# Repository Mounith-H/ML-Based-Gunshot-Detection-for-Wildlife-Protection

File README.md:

# AI-Powered Edge Gunshot Detection for Wildlife Protection

## Short summary
This repository contains firmware, hardware integration code, and supporting artifacts for an edge device that detects gunshot-like events using a Raspberry Pi Pico. The device performs on-device audio capture and inference, attaches GPS coordinates, and reports events over an NRF24L01 wireless link. The primary goals are real-time detection, low power operation, and field deployability for anti-poaching monitoring.

## Status
- Development: Feature-complete for core sensing, radio communication, GPS and power management on the Pico hardware.
- Machine learning: A TensorFlow Lite quantized model and export artifacts are provided; on-device inference integration is in progress.

Key completed items
- Audio input: INMP441 I2S microphone with PIO/DMA sampling.
- Location: NEO-6M GPS integration and basic NMEA parsing.
- Radio: NRF24L01 packet transmission with fragmentation and retries.
- Power: IP5306 power management using a PIO-driven PWM (continuous KEY pulsing) for reliable operation.
- Architecture: Dual-core Pico split (system/core tasks and audio/inference tasks) with robust initialization and error handling.

Planned / in development
- Finalize TensorFlow Lite inference on Pico and optimize model runtime.
- Optional mesh networking, encryption and acknowledgments.

## Repository contents (high level)
- `Raspberry_pi_pico/`, `inference-app/` – Pico firmware and build files.
- `python/` – training artifacts, quantized model (`gunshot_model_quant.tflite`), and helper notebooks.
- `python/dataset/` – dataset organization (environment and gunshot recordings) used for model training (see Data Availability).
- `figures_data/`, `metrics/` – plots, model metrics and training logs.
- `PCB/`, `lib/` – hardware design files and helper libraries.

## Data Availability (journal-ready statement)
All code required to build and run the device is included in this repository. The following datasets and artifacts are available as follows:

- Trained model: A quantized TensorFlow Lite model is included in `python/gunshot_model_quant.tflite` and additional exported models are in `python/exported_models/`.
- Processed training artifacts (training logs, metrics, and figure data) are included in `figures_data/` and `metrics/`.
- Raw audio recordings used for training (environmental and gunshot audio) are not included in this repository because of size and privacy/ethical constraints. Access to raw audio may be provided on reasonable request to the corresponding author for research purposes, subject to data sharing agreements.

If you need the raw audio files, preprocessed feature dumps, or a permanent DOI for the dataset, please contact the project maintainers (see Contact below). We can provide guidance to reproduce the training from raw data using the Jupyter notebook `python/model_training_quantization_jupyter.ipynb`.

Assumptions: The repository contains the trained model and training outputs, but large raw audio datasets are hosted externally or provided upon request. If you will publish this work in a journal and require a public dataset DOI, please tell us and we can prepare a dataset package for deposition (not currently included in this repo).

## Hardware
Components used in development
- Raspberry Pi Pico
- INMP441 digital microphone (I2S)
- NEO-6M GPS module
- NRF24L01 radio module
- IP5306 power-management IC

Power handling notes
- IP5306 `KEY` pin is driven by a PIO-based PWM to keep the power module enabled. The firmware contains a PIO state machine that pulses the `KEY` line with sufficient frequency and duty cycle to maintain power without manual intervention.
## Build and usage (Pico firmware)

Prerequisites

1. CMake >= 3.12
2. Raspberry Pi Pico SDK installed and `PICO_SDK_PATH` set in your environment

Quick build

1. From the firmware directory (for example `Raspberry_pi_pico/` or `inference-app/`):
   - mkdir build
   - cd build
   - cmake ..
   - make (or your platform's build tool)

2. Flashing

- Put the Pico into BOOTSEL mode and copy the generated `.uf2` file onto the Pico mass-storage device.

For exact build steps see the subdirectory `Raspberry_pi_pico/README.md` or `inference-app/README.md` (if present).

## Reproducing training
- A Jupyter notebook `python/model_training_quantization_jupyter.ipynb` demonstrates model training and quantization steps used to generate the included TFLite model. Use the `python/` directory for scripts and artifacts.

## Data sources and citations
The training used a combination of publicly available environmental and gunshot audio datasets. Below are the sources and citation information (BibTeX and IEEE formats).

1) E. Aydemir, "Gunshot audio dataset," Kaggle, 2021. [Online]. Available: https://www.kaggle.com/datasets/emrahaydemr/gunshot-audio-dataset. [Accessed: Oct. 11, 2025].

2) R. Kabealo and S. J. Wyatt, "Gunshot/Gunfire Audio Dataset," Zenodo, Jul. 2022, doi: 10.5281/zenodo.7004819. [Online]. Available: https://doi.org/10.5281/zenodo.7004819. [Accessed: Oct. 11, 2025].

3) K. J. Piczak, "ESC: Dataset for Environmental Sound Classification," in Proc. 23rd Annual ACM Conference on Multimedia, Brisbane, Australia, Oct. 2015, pp. 1015–1018, doi: 10.1145/2733373.2806390. [Online]. Available: http://dl.acm.org/citation.cfm?doid=2733373.2806390. [Accessed: Oct. 11, 2025].

## License and contact
- License: See `LICENSE` at the repository root for license terms.
- Contact / corresponding author: add a preferred contact email or GitHub handle here.

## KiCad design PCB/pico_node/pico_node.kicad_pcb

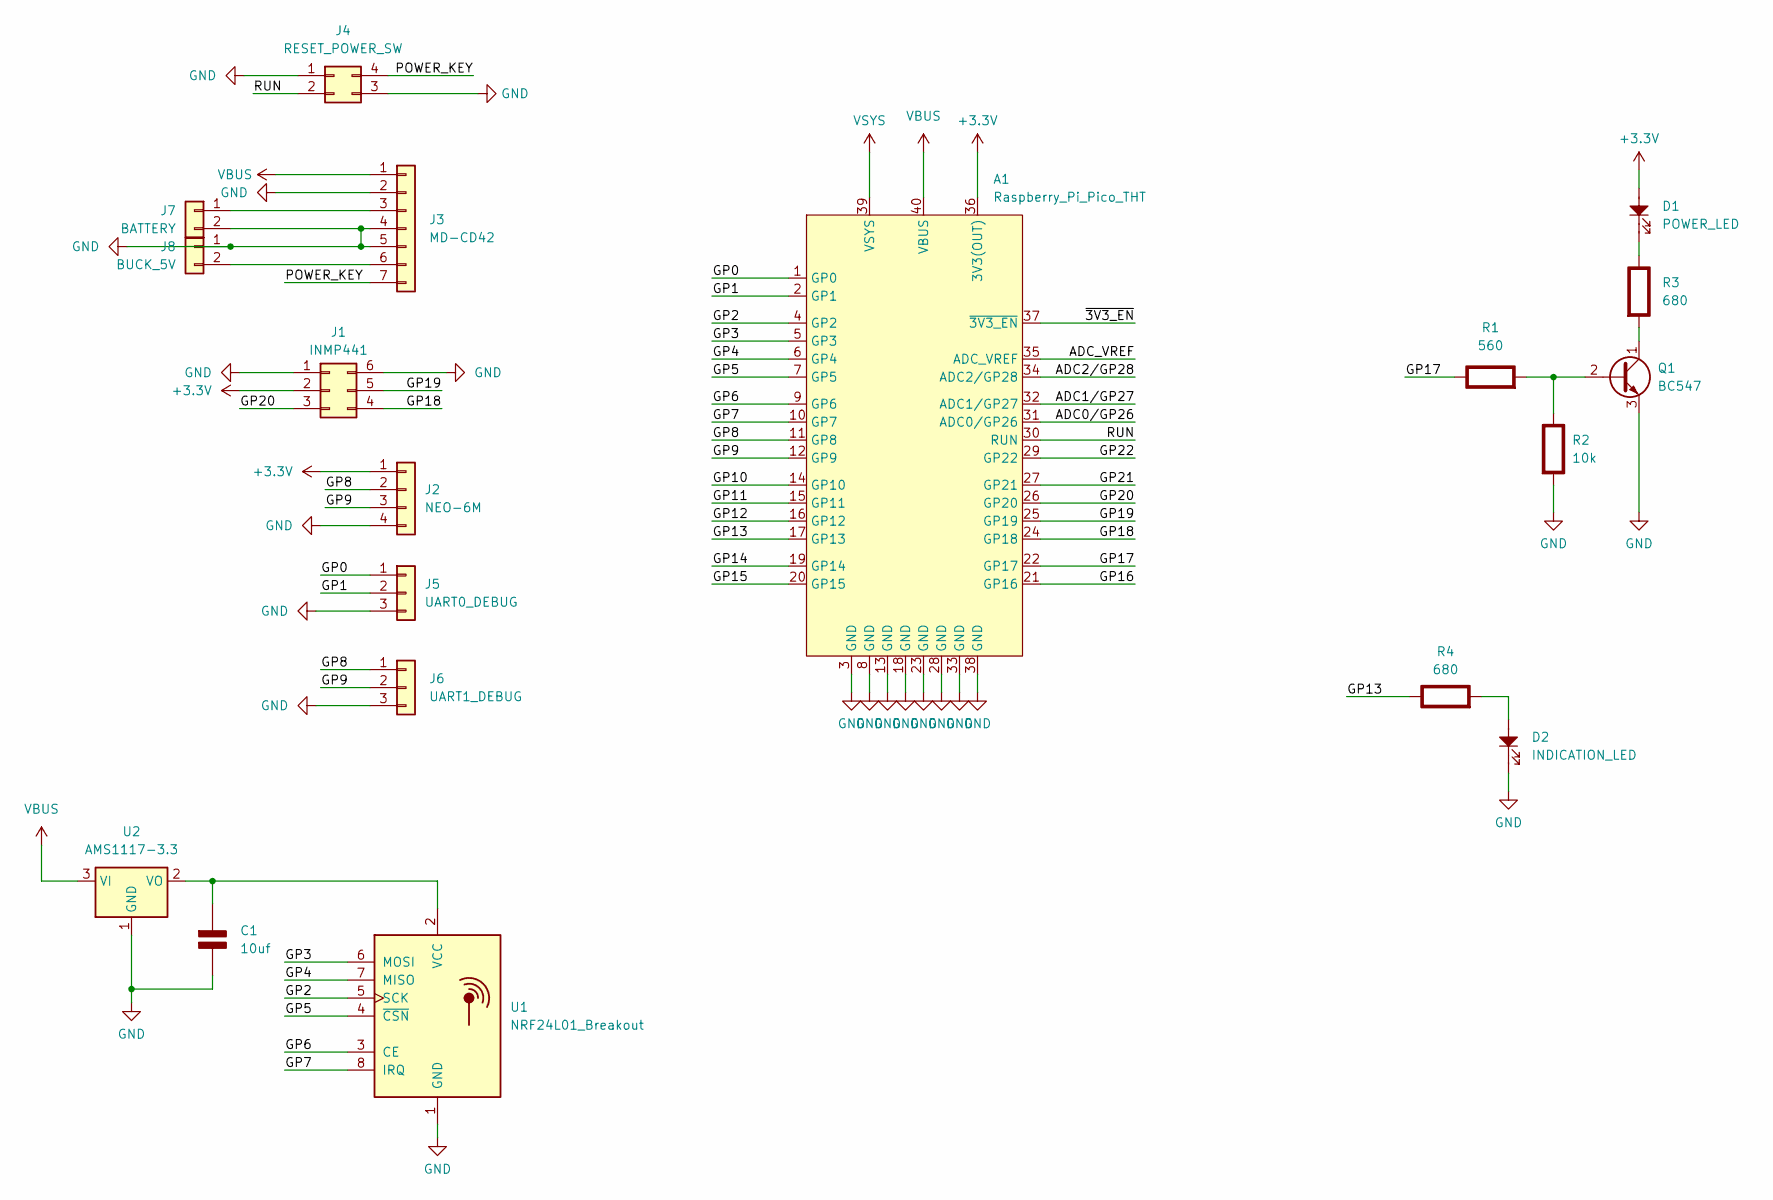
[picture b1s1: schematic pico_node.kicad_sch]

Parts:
A1: Raspberry_Pi_Pico_THT; raspberry_pi_pico_THT
C1: 10uf; CP_EIA-3528-21_Kemet-B_Pad1.50x2.35mm_HandSolder; Rating V
D1: POWER_LED; LED_D5.0mm
D2: INDICATION_LED; LED_D5.0mm
J1: INMP441; PinHeader_2x03_P2.54mm_Vertical
J2: NEO-6M; PinHeader_1x04_P2.54mm_Vertical
J3: MD-CD42; PinHeader_1x07_P2.54mm_Vertical
J4: RESET_POWER_SW; PinHeader_2x02_P2.54mm_Vertical
J5: UART0_DEBUG; PinHeader_1x03_P2.54mm_Vertical
J6: UART1_DEBUG; PinHeader_1x03_P2.54mm_Vertical
J7: BATTERY; JST_XH_B2B-XH-A_1x02_P2.50mm_Vertical
J8: BUCK_5V; PinSocket_1x02_P2.54mm_Vertical
Q1: BC547; TO-92_Inline_Wide
R1: 560; R_Axial_DIN0207_L6.3mm_D2.5mm_P10.16mm_Horizontal; Rating W
R2: 10k; R_Axial_DIN0207_L6.3mm_D2.5mm_P10.16mm_Horizontal; Rating W
R3: 680; R_1210_3225Metric_Pad1.30x2.65mm_HandSolder; Rating W
R4: 680; R_Axial_DIN0207_L6.3mm_D2.5mm_P10.16mm_Horizontal; Rating W
U1: NRF24L01_Breakout; nRF24L01_Breakout
U2: AMS1117-3.3; SOT-223-3_TabPin2

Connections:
+3.3V: A1.36 (3V3(OUT)), D1.2, J1.2, J2.1
/ADC0/GP26: A1.31 (ADC0/GP26)
/ADC1/GP27: A1.32 (ADC1/GP27)
/ADC2/GP28: A1.34 (ADC2/GP28)
/ADC_VREF: A1.35 (ADC_VREF)
/GP0: A1.1 (GP0), J5.1
/GP1: A1.2 (GP1), J5.2
/GP2: A1.4 (GP2), U1.5 (SCK)
/GP3: A1.5 (GP3), U1.6 (MOSI)
/GP4: A1.6 (GP4), U1.7 (MISO)
/GP5: A1.7 (GP5), U1.4 (~CSN)
/GP6: A1.9 (GP6), U1.3 (CE)
/GP7: A1.10 (GP7), U1.8 (IRQ)
/GP8: A1.11 (GP8), J2.2, J6.1
/GP9: A1.12 (GP9), J2.3, J6.2
/GP10: A1.14 (GP10)
/GP11: A1.15 (GP11)
/GP12: A1.16 (GP12)
/GP13: A1.17 (GP13), R4.1 (+)
/GP14: A1.19 (GP14)
/GP15: A1.20 (GP15)
/GP16: A1.21 (GP16)
/GP17: A1.22 (GP17), R1.1 (+)
/GP18: A1.24 (GP18), J1.4
/GP19: A1.25 (GP19), J1.5
/GP20: A1.26 (GP20), J1.3
/GP21: A1.27 (GP21)
/GP22: A1.29 (GP22)
/POWER_KEY: J3.7, J4.4
/RUN: A1.30 (RUN), J4.2
/~3V3_EN: A1.37 (~3V3_EN)
GND: A1.3 (GND), A1.8 (GND), A1.13 (GND), A1.18 (GND), A1.23 (GND), A1.28 (GND), A1.33 (GND), A1.38 (GND), C1.2 (-), D2.1, J1.1, J1.6, J2.4, J3.2, J3.4, J3.5, J4.1, J4.3, J5.3, J6.3, J7.2, J8.1, Q1.3 (E), R2.2 (-), U1.1 (GND), U2.1 (GND)
unnamed: C1.1 (+), U1.2 (VCC), U2.2 (VO)
unnamed: J3.3, J7.1
unnamed: J3.6, J8.2
unnamed: Q1.2 (B), R1.2 (-), R2.1 (+)
unnamed: Q1.1 (C), R3.2 (-)
unnamed: D1.1, R3.1 (+)
unnamed: D2.2, R4.2 (-)
VBUS: A1.40 (VBUS), J3.1, U2.3 (VI)
VSYS: A1.39 (VSYS)

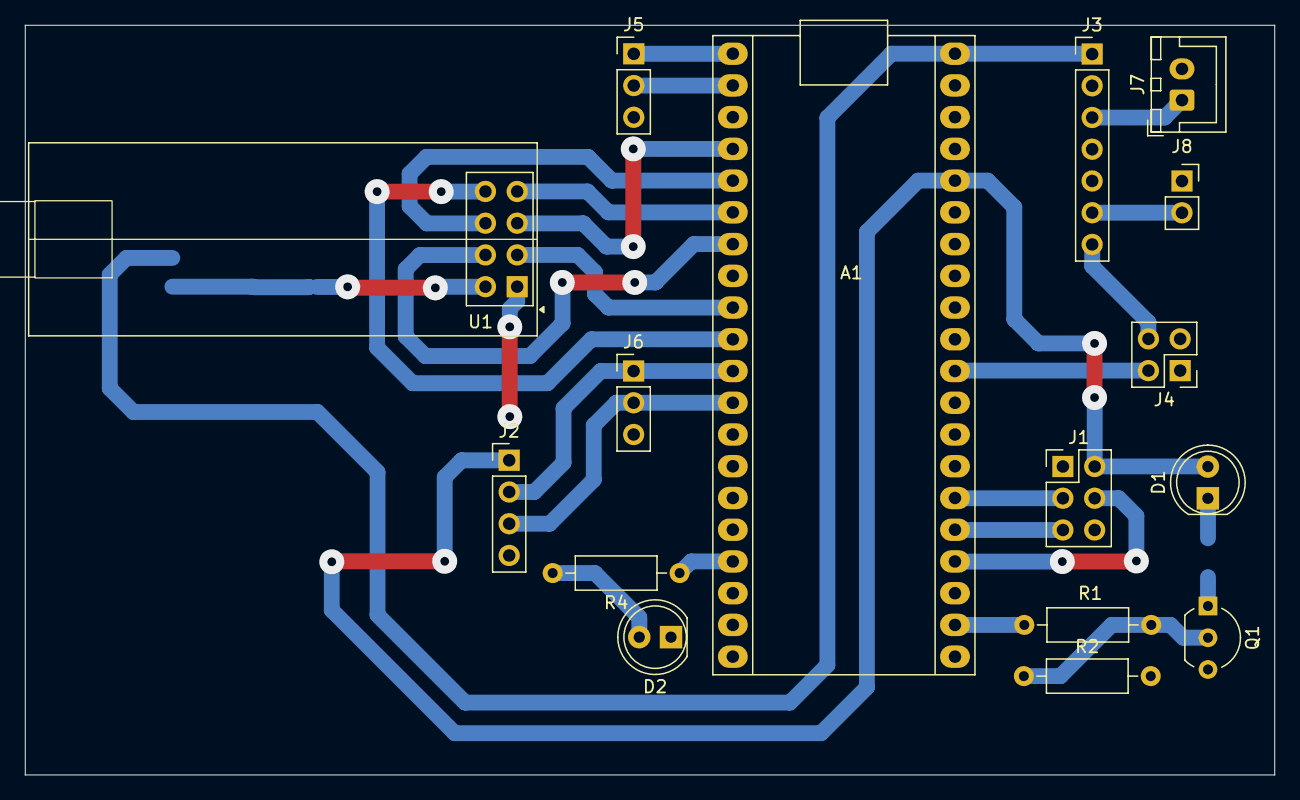
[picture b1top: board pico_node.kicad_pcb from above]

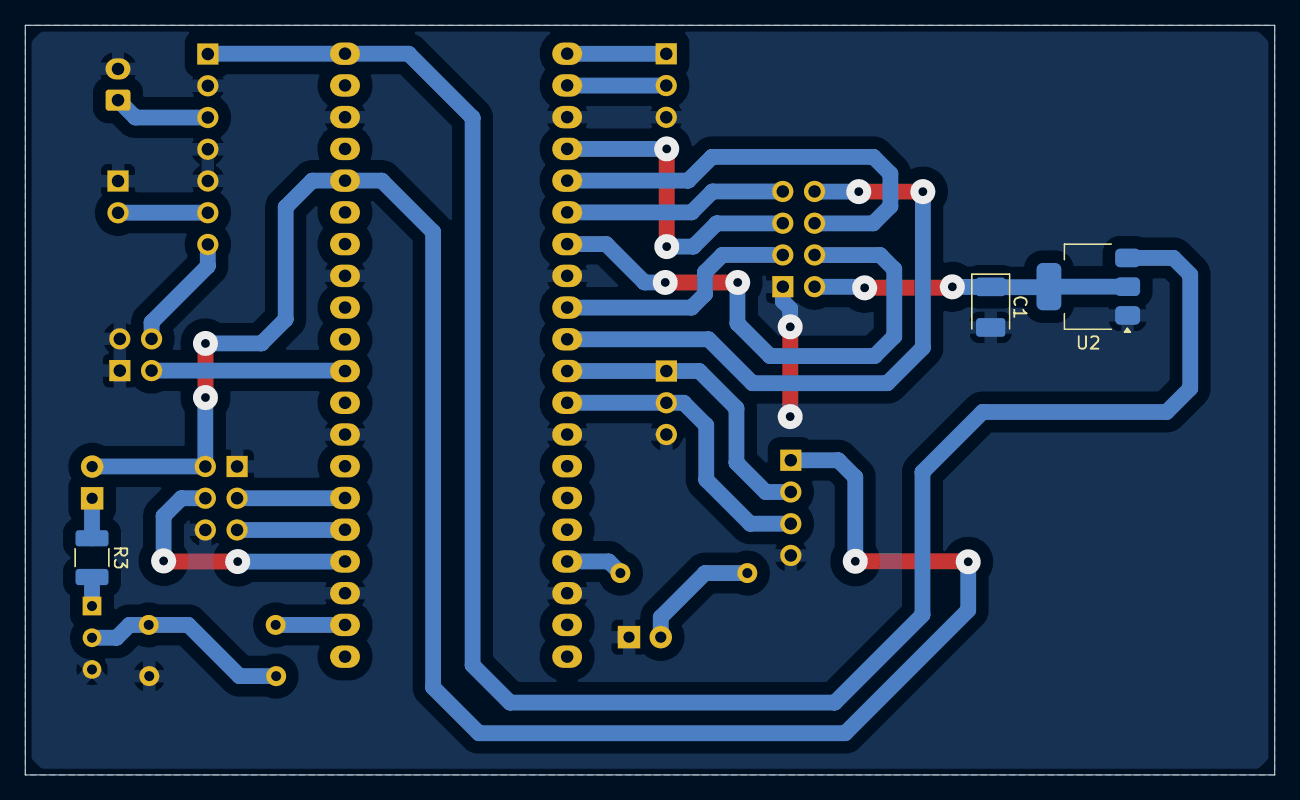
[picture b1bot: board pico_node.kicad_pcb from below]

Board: 2 copper layers, 100.0 x 60.0 mm, 19 parts (3 on the bottom side), 27 nets.

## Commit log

2025-06-08 implemented pico_node code pending to implement tensorflow working on PCB
2025-06-08 updated PCB
2025-06-08 3d Models added
2025-06-08 readme update
2025-06-08 added setup scrpt
2025-06-10 Updated setup scripts
2025-06-10 Update on pico_node pcb
2025-06-13 updated code added stm32
2025-10-23 AI-PEGD gunshot detection system
